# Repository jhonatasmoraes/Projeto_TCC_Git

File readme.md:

Neste projeto será colocado as informações do programa construído para o meu projeto de TCC.

26/02/23 Criação dos arquivos no Git    

-> A

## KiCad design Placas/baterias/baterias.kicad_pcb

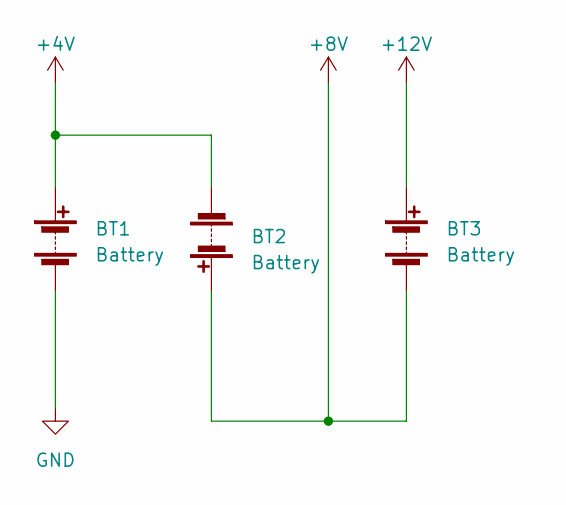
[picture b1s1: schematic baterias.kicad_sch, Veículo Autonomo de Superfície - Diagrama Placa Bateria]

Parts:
BT1, BT2, BT3: Battery; BatteryHolder_MPD_BH-18650-PC2

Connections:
+4V: BT1.1 (+), BT2.2 (-)
+8V: BT2.1 (+), BT3.2 (-)
+12V: BT3.1 (+)
GND: BT1.2 (-)

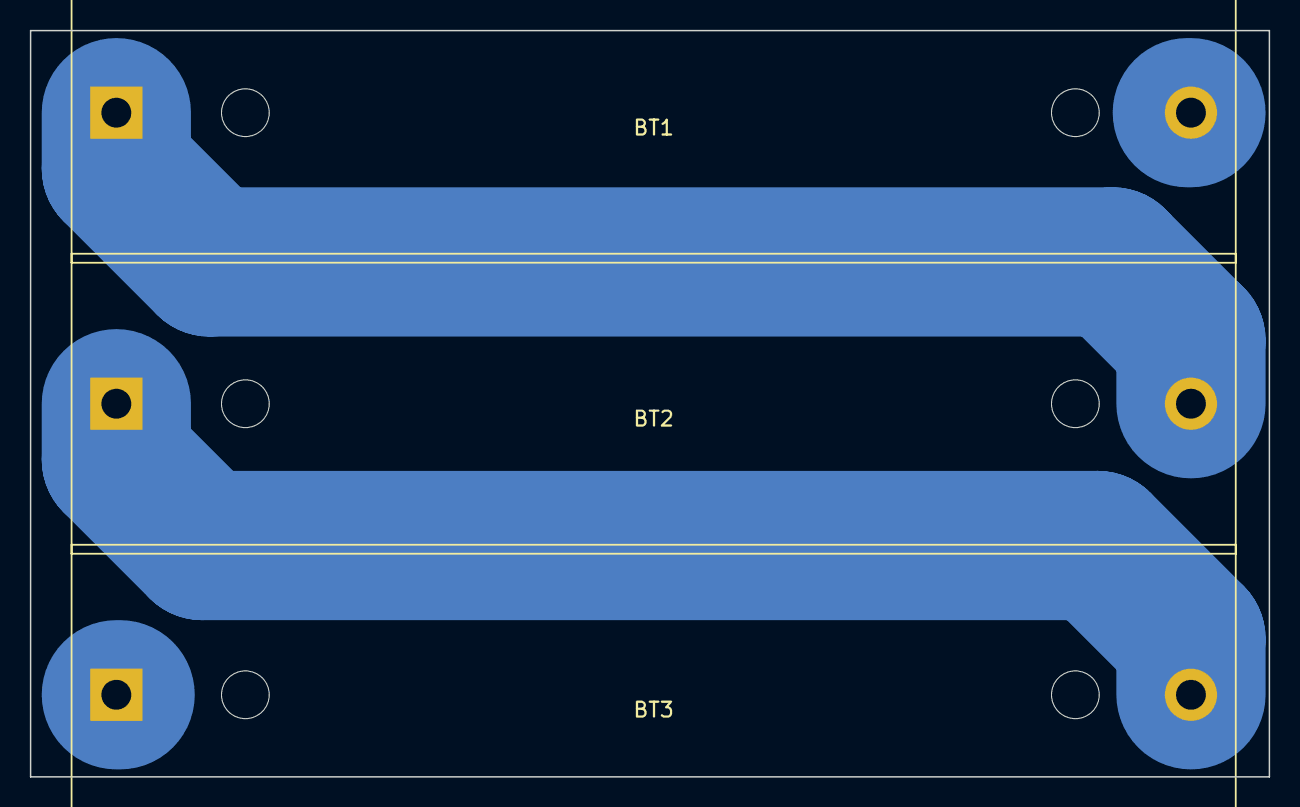
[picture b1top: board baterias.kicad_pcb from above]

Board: 2 copper layers, 83.0 x 50.0 mm, 3 parts (0 on the bottom side), 2 nets.

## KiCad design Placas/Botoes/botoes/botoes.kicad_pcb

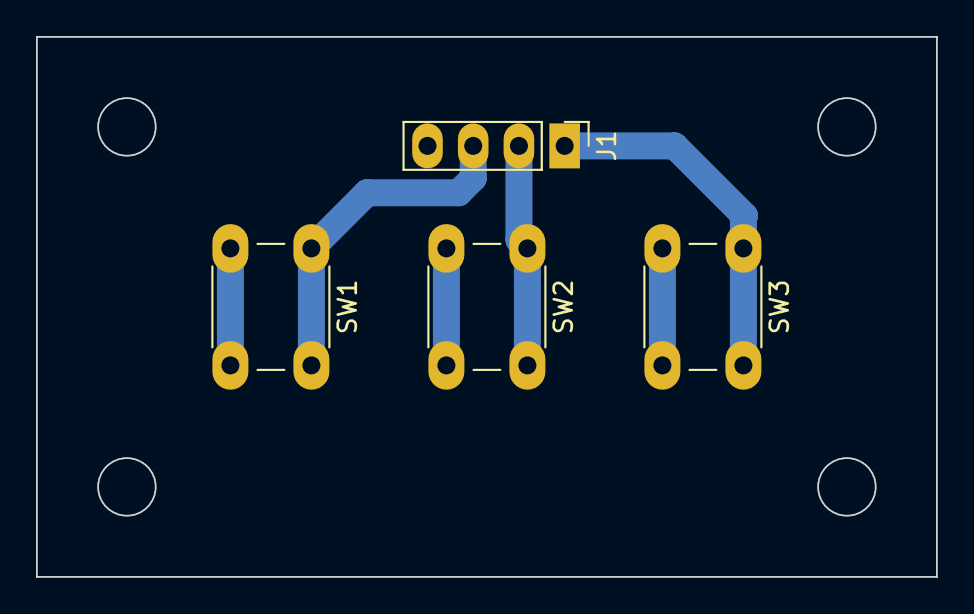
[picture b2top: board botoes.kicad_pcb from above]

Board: 2 copper layers, 50.0 x 30.0 mm, 4 parts (0 on the bottom side), 4 nets.

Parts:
J1: Conn_01x04_Pin; PinHeader_1x04_P2.54mm_Vertical
SW1: Sobe; SW_PUSH_6mm
SW2: Desce; SW_PUSH_6mm
SW3: Entra; SW_PUSH_6mm

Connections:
GND: J1.4, SW1.2, SW2.2, SW3.2
unnamed: J1.1, SW3.1
unnamed: J1.2, SW2.1
unnamed: J1.3, SW1.1

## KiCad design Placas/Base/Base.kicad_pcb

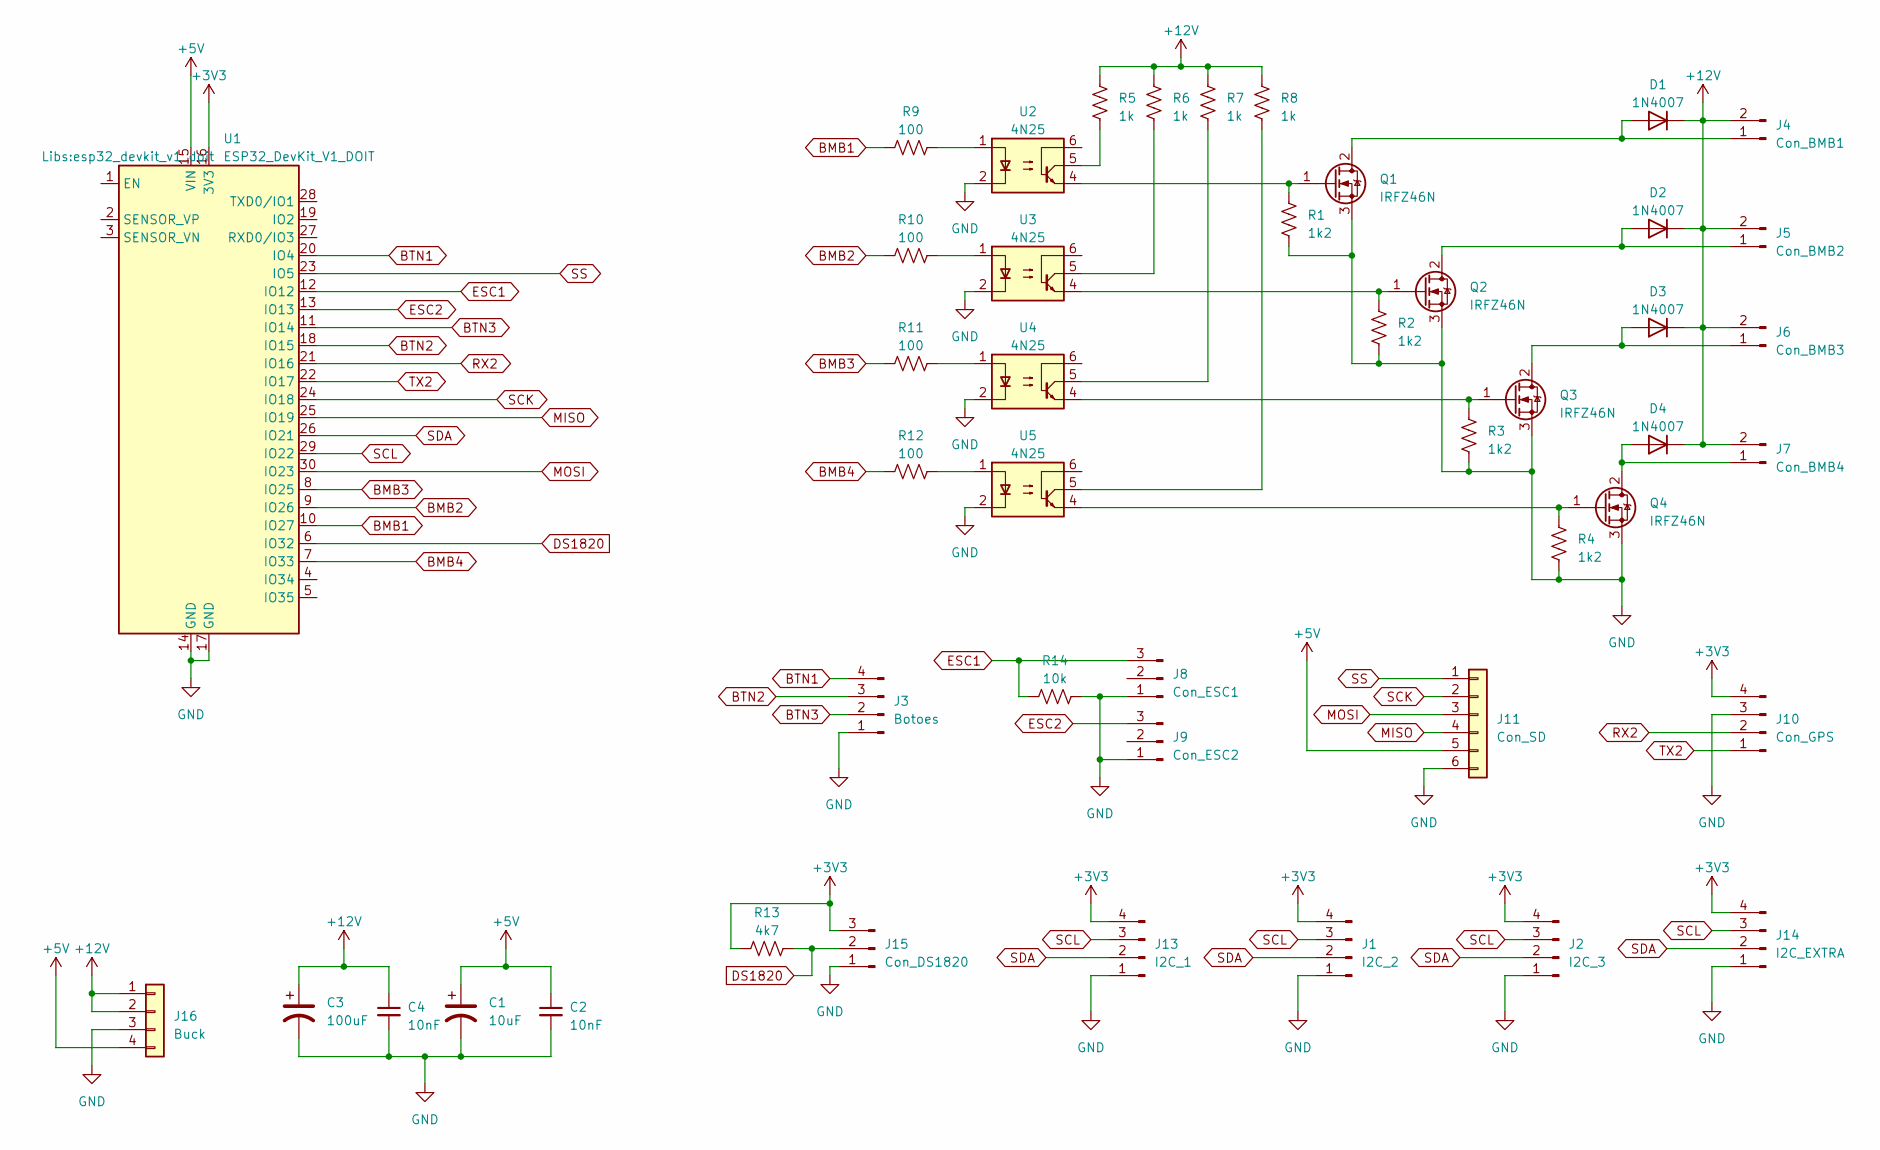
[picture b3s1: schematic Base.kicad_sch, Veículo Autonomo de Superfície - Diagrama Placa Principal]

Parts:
C1: 10uF; CP_Radial_D8.0mm_P3.50mm
C2, C4: 10nF; C_Disc_D7.0mm_W2.5mm_P5.00mm
C3: 100uF; CP_Radial_D8.0mm_P3.50mm
D1, D2, D3, D4: 1N4007; D_DO-41_SOD81_P10.16mm_Horizontal
J1: I2C_2; JST_XH_B4B-XH-A_1x04_P2.50mm_Vertical
J2: I2C_3; JST_XH_B4B-XH-A_1x04_P2.50mm_Vertical
J3: Botoes; JST_XH_B4B-XH-A_1x04_P2.50mm_Vertical
J4: Con_BMB1; JST_XH_B2B-XH-A_1x02_P2.50mm_Vertical
J5: Con_BMB2; JST_XH_B2B-XH-A_1x02_P2.50mm_Vertical
J6: Con_BMB3; JST_XH_B2B-XH-A_1x02_P2.50mm_Vertical
J7: Con_BMB4; JST_XH_B2B-XH-A_1x02_P2.50mm_Vertical
J8: Con_ESC1; PinHeader_1x03_P2.54mm_Vertical
J9: Con_ESC2; PinHeader_1x03_P2.54mm_Vertical
J10: Con_GPS; JST_XH_B4B-XH-A_1x04_P2.50mm_Vertical
J11: Con_SD; PinHeader_1x06_P2.54mm_Vertical
J13: I2C_1; JST_XH_B4B-XH-A_1x04_P2.50mm_Vertical
J14: I2C_EXTRA; JST_XH_B4B-XH-A_1x04_P2.50mm_Vertical
J15: Con_DS1820; JST_XH_B3B-XH-A_1x03_P2.50mm_Vertical
J16: Buck; PinHeader_1x04_P2.54mm_Horizontal
Q1, Q2, Q3, Q4: IRFZ46N; TO-220-3_Vertical
R1, R2, R3, R4: 1k2; R_Axial_DIN0207_L6.3mm_D2.5mm_P10.16mm_Horizontal
R5, R6, R7, R8: 1k; R_Axial_DIN0207_L6.3mm_D2.5mm_P10.16mm_Horizontal
R9, R10, R11, R12: 100; R_Axial_DIN0207_L6.3mm_D2.5mm_P10.16mm_Horizontal
R13: 4k7; R_Axial_DIN0207_L6.3mm_D2.5mm_P10.16mm_Horizontal
R14: 10k; R_Axial_DIN0207_L6.3mm_D2.5mm_P10.16mm_Horizontal
U1: ESP32_DevKit_V1_DOIT; esp32_devkit_v1_doit
U2, U3, U4, U5: 4N25; DIP-6_W7.62mm

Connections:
+3V3: J1.4, J2.4, J10.4, J13.4, J14.4, J15.3, R13.1, U1.16 (3V3)
+5V: C1.1, C2.1, J11.5, J16.4, U1.15 (VIN)
+12V: C3.1, C4.1, D1.1 (K), D2.1 (K), D3.1 (K), D4.1 (K), J4.2, J5.2, J6.2, J7.2, J16.1, J16.2, R5.1, R6.1, R7.1, R8.1
BMB1: R9.1, U1.10 (IO27)
BMB2: R10.1, U1.9 (IO26)
BMB3: R11.1, U1.8 (IO25)
BMB4: R12.1, U1.7 (IO33)
BTN1: J3.4, U1.20 (IO4)
BTN2: J3.3, U1.18 (IO15)
BTN3: J3.2, U1.11 (IO14)
DS1820: J15.2, R13.2, U1.6 (IO32)
ESC1: J8.3, R14.1, U1.12 (IO12)
ESC2: J9.3, U1.13 (IO13)
GND: C1.2, C2.2, C3.2, C4.2, J1.1, J2.1, J3.1, J8.1, J9.1, J10.3, J11.6, J13.1, J14.1, J15.1, J16.3, Q1.3 (S), Q2.3 (S), Q3.3 (S), Q4.3 (S), R1.2, R2.2, R3.2, R4.2, R14.2, U1.14 (GND), U1.17 (GND), U2.2, U3.2, U4.2, U5.2
MISO: J11.4, U1.25 (IO19)
MOSI: J11.3, U1.30 (IO23)
unnamed: D1.2 (A), J4.1, Q1.2 (D)
unnamed: D2.2 (A), J5.1, Q2.2 (D)
unnamed: D3.2 (A), J6.1, Q3.2 (D)
unnamed: D4.2 (A), J7.1, Q4.2 (D)
unnamed: Q1.1 (G), R1.1, U2.4
unnamed: Q2.1 (G), R2.1, U3.4
unnamed: Q3.1 (G), R3.1, U4.4
unnamed: Q4.1 (G), R4.1, U5.4
unnamed: R5.2, U2.5
unnamed: R6.2, U3.5
unnamed: R7.2, U4.5
unnamed: R8.2, U5.5
unnamed: R9.2, U2.1
unnamed: R10.2, U3.1
unnamed: R11.2, U4.1
unnamed: R12.2, U5.1
RX2: J10.2, U1.21 (IO16)
SCK: J11.2, U1.24 (IO18)
SCL: J1.3, J2.3, J13.3, J14.3, U1.29 (IO22)
SDA: J1.2, J2.2, J13.2, J14.2, U1.26 (IO21)
SS: J11.1, U1.23 (IO5)
TX2: J10.1, U1.22 (IO17)

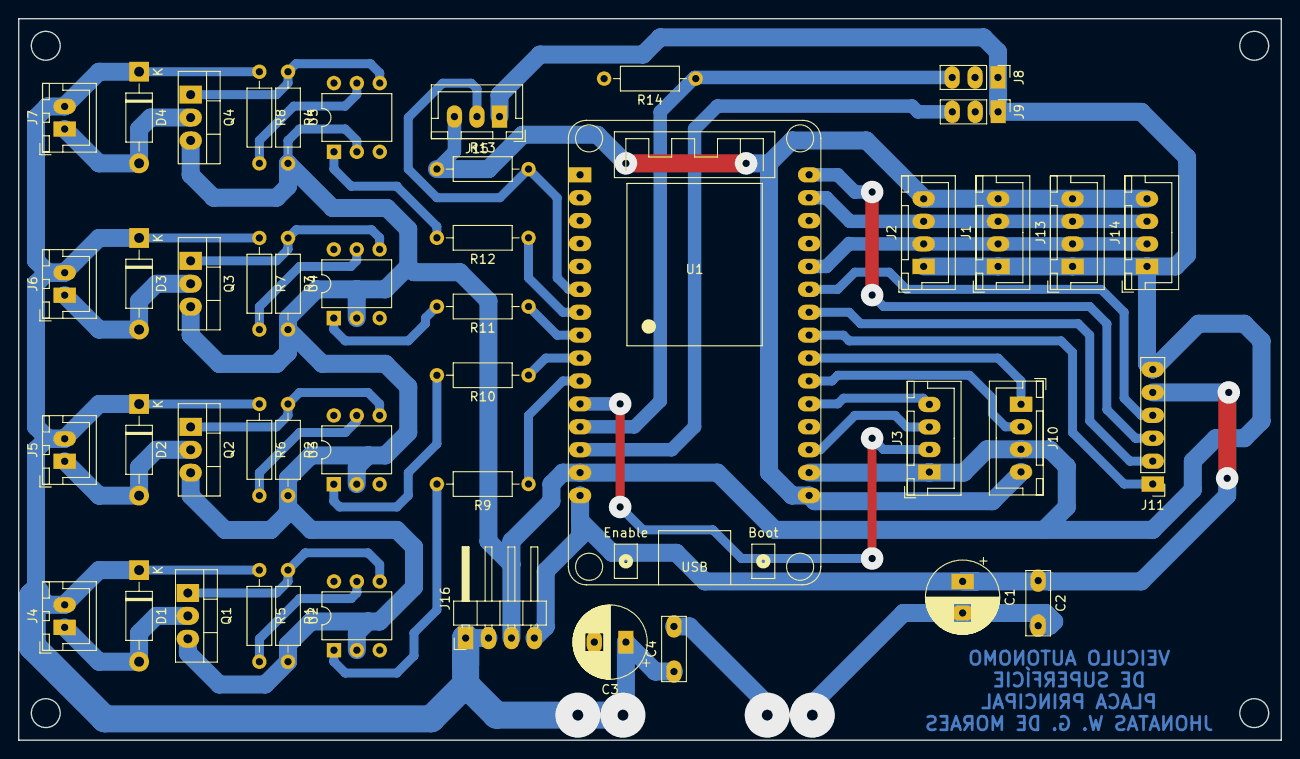
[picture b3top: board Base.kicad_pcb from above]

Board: 2 copper layers, 140.0 x 80.0 mm, 46 parts (0 on the bottom side), 38 nets.

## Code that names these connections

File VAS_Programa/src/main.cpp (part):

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      -> GPIO 19 -- MISO
      -> GPIO 23 -- MOSI
    Pinos conectados aos botoes (Pull-up interno)
      -> GPIO 4  -- BTN1
      -> GPIO 14 -- BTN3 (Apresenta PWM durante boot)
      -> GPIO 15 -- BTN2 (Apresenta PWM durante boot)
    Pinos conectados as bombas
      -> GPIO 25 -- BMB3
      -> GPIO 26 -- BMB2
      -> GPIO 27 -- BMB1
      -> GPIO 33 -- BMB4
    Pino conectado ao termometro D18S20 (OneWire)
      -> GPIO 32 -- D18S20
    Pinos conectados aos ESCs
      -> GPIO 12 -- ESC1 ou ESCA  (precisa estar com resistor de pull-down se conectado ao servo)
      -> GPIO 13 -- ESC2 ou ESCB
    Pinos nao conectados (abertos)
      -> GPIO 2  -- NC  (LED on board)
      -> GPIX 34 -- NC  
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//Pinos GPIO
const int ESCA_Pin = 12;
const int ESCB_Pin = 13;
const int btn_1 = 15; //Botao anterior ou desce laranja btn2 se possivel, trocar no plug
const int btn_2 = 4; //Botao seguinte ou sobe vermelho btn1 
const int btn_3 = 14; //Botao entra13 amarelo btn3
const int bomba1 = 33;
const int bomba2 = 25;
const int bomba3 = 26;
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
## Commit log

2023-02-26 primeiro commit
2023-02-26 Teste de atualização do arquivo
2023-02-26 Adição dos arquivos do programa
2023-02-26 Primeira compilação sem nada adicionado
2023-02-26 Adicionado o desvio magnetico para os testes
2023-02-26 Adicionadas as bibliotecas e inicializadas algumas variaveis e parametros
2023-02-26 Adicionadas mais bibliotecas e problemas com magnetometro
2023-03-02 Adicionado a correção de calibração magnetometro e pré adicionado os botoes
2023-03-13 Adicionados os menus e itens bitmaps
2023-03-19 adicionado os comandos de ESC
2023-04-02 Adicionado a leitura de dados do cartão SD e adicionado alguns comentarios
2023-04-02 Adicionado o espaço para a função navegar e separadores
2023-05-03 Update antes das demais mudanças 03-05-23
2023-05-07 Update finalização das estruturas, exceto principal
2023-05-08 Update final 07/05
2023-07-02 Update final 01/07
